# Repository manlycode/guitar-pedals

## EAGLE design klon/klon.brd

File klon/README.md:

* https://www.electrosmash.com/klon-centaur-analysis

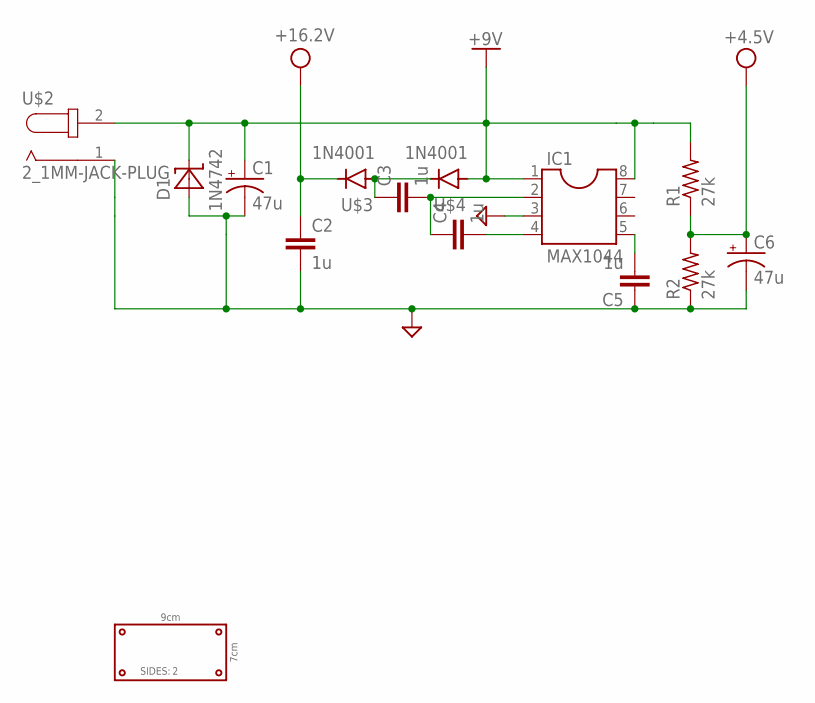
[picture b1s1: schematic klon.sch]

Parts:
C1, C6: 47u; C-E-0.1_0.15
C2, C3, C4, C5: 1u; C-MM-0.2_0.1
D1: 1N4742; DO41-7.6
IC1: MAX1044; DIL08
R1, R2: 27k; 0204/7
U$1: GREEN-2-SIDED9X7; 9X7_CM
U$2: 2_1MM-JACK-PLUG; 1X02
U$3, U$4: 1N4001; DO41-7

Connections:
+4.5V: C6.+, R1.1, R2.2
+9V: C1.+, D1.C, IC1.1, IC1.8, R1.2, U$2.2 (GND), U$4.A
+16.2V: C2.1, U$3.C
GND: C1.-, C2.2, C5.1, C6.-, D1.A, IC1.3, R2.1, U$2.1 (+9V)
unnamed: C5.2, IC1.5
unnamed: C3.1, U$3.A, U$4.C
unnamed: C4.2, IC1.4
unnamed: C3.2, C4.1, IC1.2

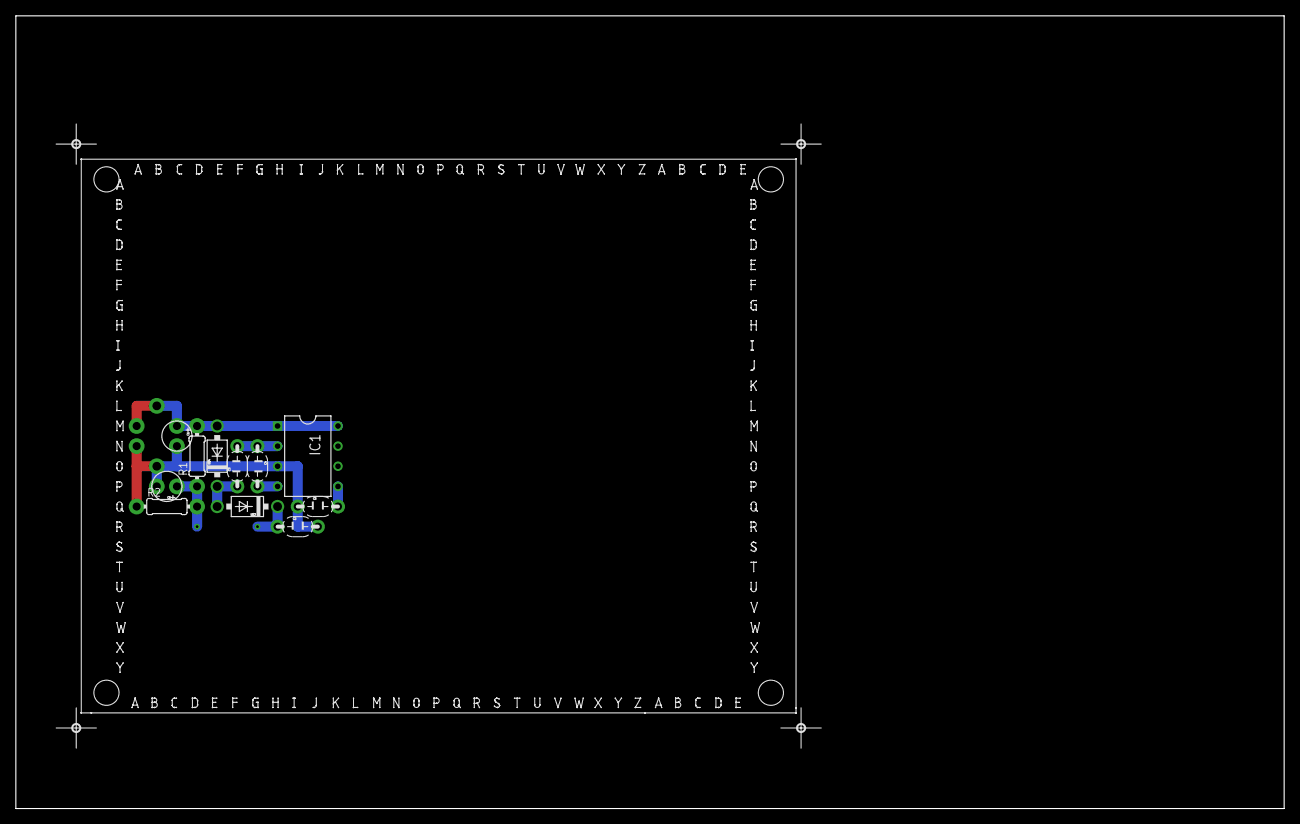
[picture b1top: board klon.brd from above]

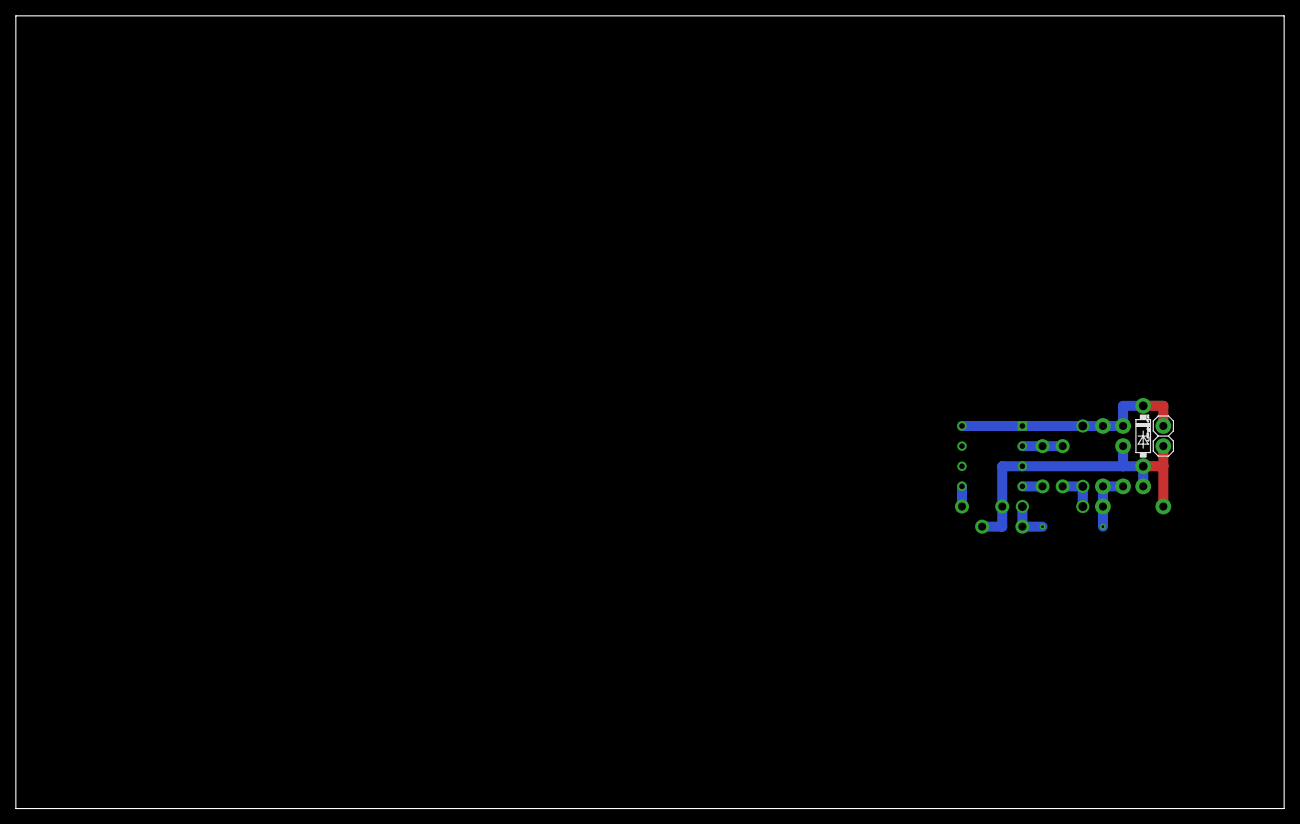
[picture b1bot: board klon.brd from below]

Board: 2 copper layers, 160.0 x 100.0 mm, 14 parts (2 on the bottom side), 8 nets.

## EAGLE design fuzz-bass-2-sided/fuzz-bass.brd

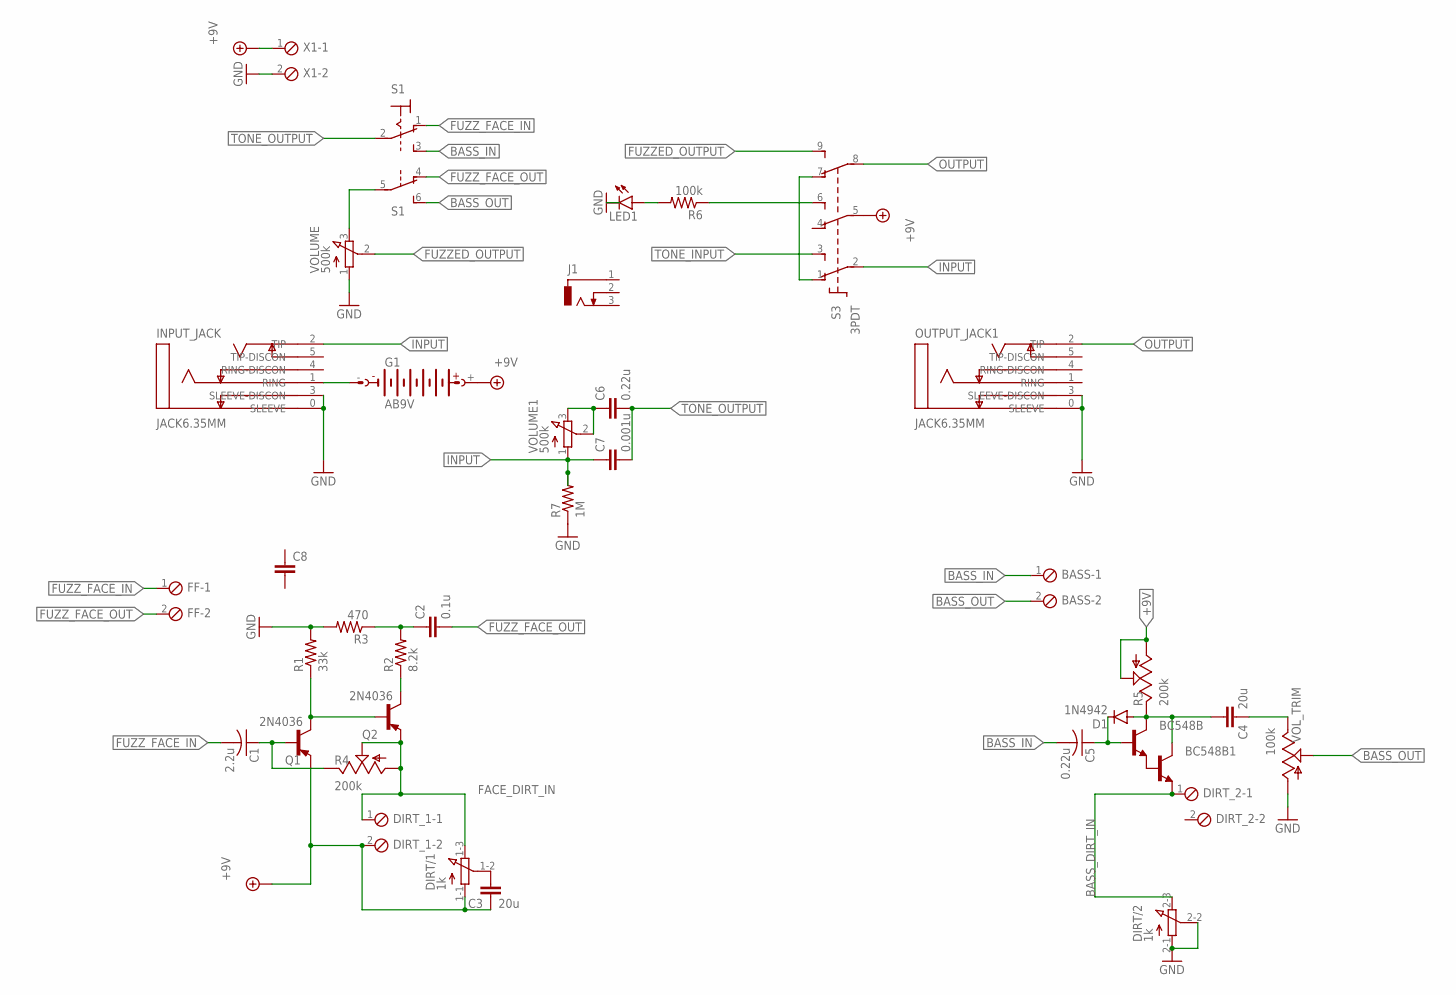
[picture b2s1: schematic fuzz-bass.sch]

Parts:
BASS: MPT2; 2POL254
BC548B, BC548B1: -NPN-TO92L; TO92L
C1: 2.2u; C025-050X050
C2: 0.1u; C050-024X044
C3, C4: 20u; C025-030X050
C5: 0.22u; C025-050X050
C6: 0.22u; C050-024X044
C7: 0.001u; C050-024X044
C8: C-EU025-025X050; C025-025X050
D1: 1N4942; DO41-10
DIRT: 1k; 3RP/1610G
DIRT_1, DIRT_2: MPT2; 2POL254
FF: MPT2; 2POL254
G1: AB9V
INPUT_JACK: JACK6.35MM
J1: DCJ0303
LED1: LED3MM
OUTPUT_JACK1: JACK6.35MM
Q1, Q2: 2N4036; TO5
R1: 33k; 0204/7
R2: 8.2k; 0204/7
R3: 470; 0204/7
R4, R5: 200k; RJ9W
R6: 100k; 0204/7
R7: 1M; 0204/7
S1: M9040P2
S3: 3PDT
VOLUME, VOLUME1: 500k; 3RP/1610N
VOL_TRIM: 100k; RJ9W
X1: MPT2; 2POL254

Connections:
+9V: C3.1, DIRT.1-1 (A), DIRT_1.2, G1.+, Q1.1 (E), R5.A, R5.S, S3.5 (P2), X1.1
BASS_DIRT_IN: BC548B1.1 (E), DIRT.2-3 (E), DIRT_2.1
BASS_IN: BASS.1, C5.2, S1.3 (S)
BASS_OUT: BASS.2, S1.6 (S), VOL_TRIM.S
FACE_DIRT_IN: DIRT.1-3 (E), DIRT_1.1, Q2.1 (E), R4.A, R4.S
FUZZED_OUTPUT: S3.9 (S3), VOLUME.2 (S)
FUZZ_FACE_IN: C1.2, FF.1, S1.1 (O)
FUZZ_FACE_OUT: C2.2, FF.2, S1.4 (O)
GND: DIRT.2-1 (A), DIRT.2-2 (S), INPUT_JACK.0 (SLEEVE), INPUT_JACK.3 (SLEEVE-DISCON), LED1.K (C), OUTPUT_JACK1.0 (SLEEVE), OUTPUT_JACK1.3 (SLEEVE-DISCON), R1.2, R3.2, R7.1, VOLUME.1 (A), VOL_TRIM.A, X1.2
INPUT: C7.1, INPUT_JACK.2 (TIP), R7.2, S3.2 (P1), VOLUME1.1 (A)
unnamed: Q2.3 (C), R2.1
unnamed: C1.1, Q1.2 (B), R4.E
unnamed: Q1.3 (C), Q2.2 (B), R1.1
unnamed: C3.2, DIRT.1-2 (S)
unnamed: C2.1, R2.2, R3.1
unnamed: BC548B.1 (E), BC548B1.2 (B)
unnamed: BC548B.3 (C), BC548B1.3 (C), C4.2, D1.A, R5.E
unnamed: R6.1, S3.6 (S2)
unnamed: LED1.A, R6.2
unnamed: BC548B.2 (B), C5.1, D1.C
unnamed: C4.1, VOL_TRIM.E
unnamed: C6.1, VOLUME1.2 (S), VOLUME1.3 (E)
unnamed: S3.1 (O1), S3.7 (O3)
unnamed: G1.-, INPUT_JACK.1 (RING)
unnamed: S1.5, VOLUME.3 (E)
OUTPUT: OUTPUT_JACK1.2 (TIP), S3.8 (P3)
TONE_INPUT: S3.3 (S1)
TONE_OUTPUT: C6.2, C7.2, S1.2

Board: 2 copper layers, 36 parts (3 on the bottom side), 27 nets, no tracks yet.

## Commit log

2020-06-04 Initial commit.
2020-06-25 Add fuzz-face info.
2020-06-28 Update Readme.
2020-06-28 Add schematic
2020-10-23 Save muff-pi clone.
2020-11-03 Add board and schematic for fuzzbass.
2020-11-06 Add bass section to fuzz bass.
2020-11-09 Updates to fuzz-bass.
2021-01-26 Add Klon schematic
2021-01-26 Add boards.
2021-01-29 Add fuzzface-2-sided.
2021-01-30 Add pedal library to quickly access parts I have.
2021-01-30 Add Perfboard library
2021-01-30 Add 7x3 perfboard.
2021-01-30 Add 6x4 board.
2021-01-30 Add 7x5cm board.
2021-01-31 library tweaks.
2021-01-31 Rename library
2021-02-01 Add klon power.
2021-02-02 klon tweaks
2021-02-28 Breakout board.
2021-02-28 Klon schematic
2022-08-26 @WIP
2022-08-28 Add schematic for toaster oven.
2022-08-29 Add controller board.
2022-08-29 Add OLED display.
2022-08-29 Add encoder library.
2022-08-29 Successfully wire up encoder.
2022-08-30 Pull UI code into class.
2022-08-30 Simplify refactor.
2022-08-31 Use function pointer to display screen.
2022-08-31 Add clear methods.
2022-08-31 Change number with turns of knob.
2022-09-01 Add view to test heater timing.
2022-09-01 Zeroing in on phase angle control.
2022-09-01 Phase angle control even works when it's still connecting.
2022-09-01 bookmark before re-factor.
2022-09-01 refactor into 0venState class.
2022-09-02 Dial in and display temp voltage.
2022-09-04 Add velocity.
2022-09-05 Add tooCool to ovenstate.
2022-09-05 Update UI.
2022-09-08 Add best guess for thermistor.
2022-09-16 Add thermistor and basic unit testing framework.
2022-09-17 Rename old OvenState class.
2022-09-17 Add new OvenState project.
2022-09-17 Add timestamp macro helper.
2022-09-17 Configure velocity and acceleration for OvenState.
2022-09-17 Add spreadsheet.
2022-09-17 Add tests for predicted temp.
2022-09-17 Add predicted temp to OvenState.
2022-09-17 Add function isTooHot()/
2022-09-17 Add heating logic.
2022-09-17 Add controls for target temp.
2022-09-17 Add test for onToggleHeater.
2022-09-17 ignore binary
2022-09-17 Final tweaks before testing.
2022-09-17 Tweak for thermistor
2022-09-17 Tweak delay.
2022-09-17 Save Captures from logic.
2022-09-17 Re-factor project to enable runs from project root.
2022-09-18 Move OvenState to it's own directory.
2022-09-18 Add schedule method for Timeline.
2022-09-18 Add unit tests for scheduling.
2022-09-18 Add more tests for scheduling.
2022-09-18 Dynamically include correct headers if it's under unit test.
2022-09-18 bookmarking before moving all timeline code into header.
2022-09-18 Re-factor timeline.
2022-09-18 Successfully bind timeline to class.
2022-09-18 Timeline now working for classes.
2022-09-18 Successfully schedule ovenstate.
2022-09-18 Add *.d files to gitignore.
2022-09-18 re-factor OvenState test file.
2022-09-18 Re-factor for forwarding timestamp.
2022-09-18 Test modes for oven state.
2022-09-18 Get pins working.
2022-09-24 Add spike values for oven operation.
2022-09-24 Add TempCurve class.
2022-09-24 Add duration to TempCurve.
2022-09-24 Add deltaTemp method.
2022-09-24 Add temp curve for all states.
2022-09-25 Add more temp curve tests.
2022-09-25 Make tweaks to make thing crash less.
2022-09-25 Successfully test Full workflow.
2022-09-25 revert thermistor values back to ones for the oven.
2022-09-25 Run things a little hotter.
2022-09-26 Save before transition away from uuid.
2022-09-26 Successfully broadcasting temp and velocity data.
2022-10-01 add refrerence drawings for CAD
2022-10-01 Add 2nd display.
2024-08-21 Add noise gate stuff.
